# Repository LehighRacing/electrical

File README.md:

# hardware
Electronic Hardware Design

## Layout
- src
    - Individual hardware components
- lib
    - Library files common between components
- util
    - Utility tools

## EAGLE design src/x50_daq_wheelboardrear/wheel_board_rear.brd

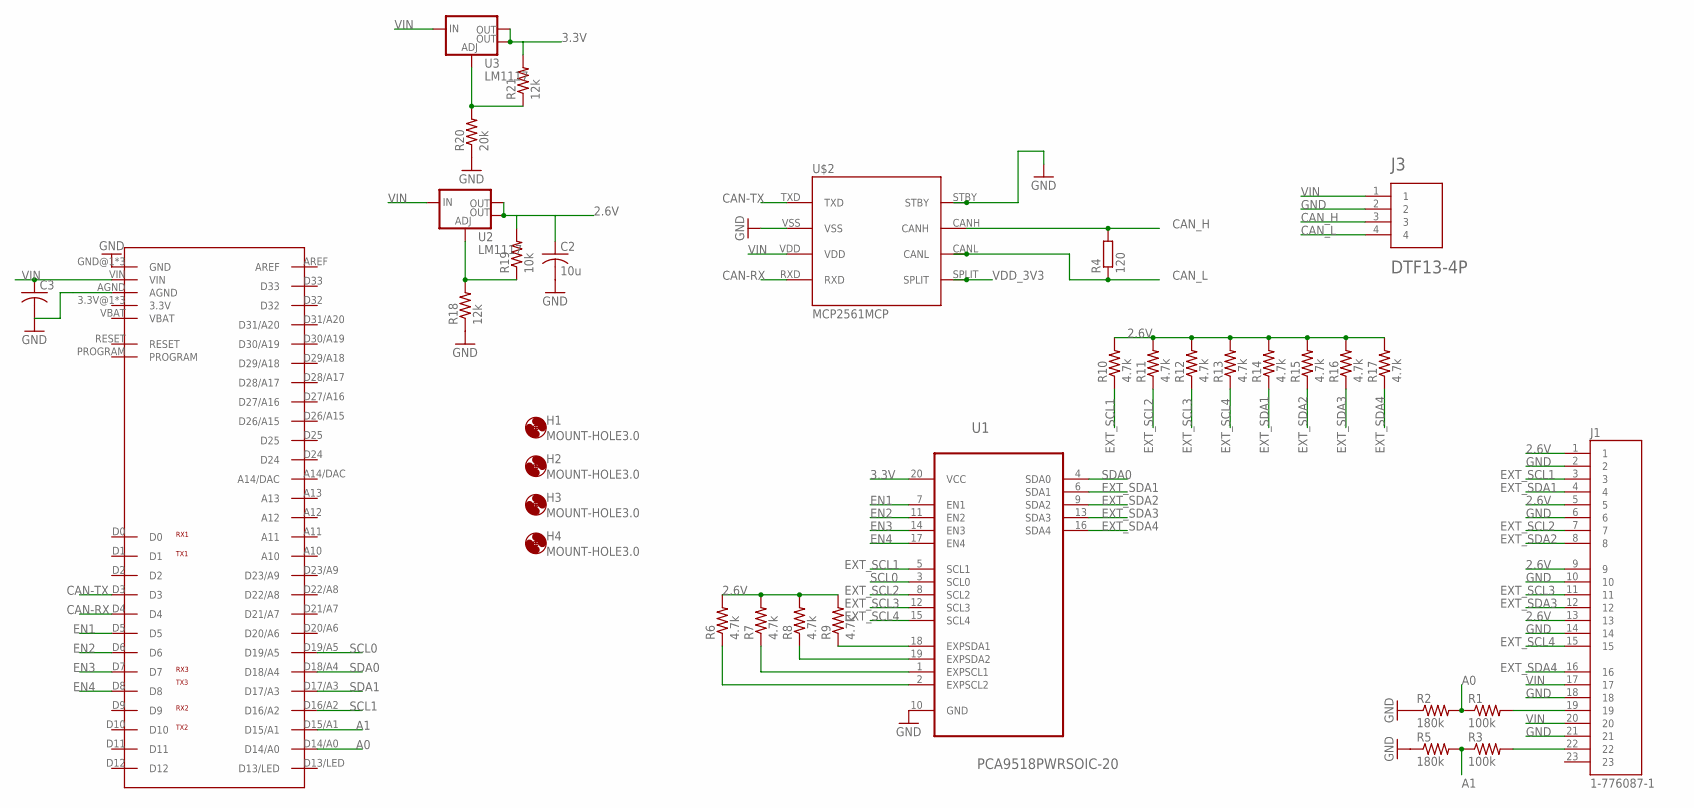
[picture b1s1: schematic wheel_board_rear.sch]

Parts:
C2: 10u; C050-024X044
C3: C-US050-024X044; C050-024X044
H1, H2, H3, H4: MOUNT-HOLE3.0; 3,0
J1: 1-776087-1; TE_1-776087-1
J3: DTF13-4P; TE_DTF13-4P
R1, R3: 100k; 0204/7
R2, R5: 180k; 0204/7
R4: 120; R0805
R6, R7, R8, R9, R10, R11, R12, R13, R14, R15, R16, R17: 4.7k; 0204/7
R18, R21: 12k; 0204/7
R19: 10k; 0204/7
R20: 20k; 0204/7
U1: PCA9518PWRSOIC-20; SOIC127P1032X265-20N
U2, U3: LM1117; SOT223
U$1: TEENSY3.1_ALL
U$2: MCP2561MCP; MCP2561_PDIP

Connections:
2.6V: C2.1, J1.1, J1.5, J1.9, J1.13, R6.2, R7.2, R8.2, R9.2, R10.2, R11.2, R12.2, R13.2, R14.2, R15.2, R16.2, R17.2, R19.2, U2.2 (OUT), U2.4 (OUT)
3.3V: R21.2, U1.20 (VCC), U3.2 (OUT), U3.4 (OUT)
A0: R1.1, R2.2, U$1.D14/A0
A1: R3.1, R5.2, U$1.D15/A1
CAN-RX: U$1.D4, U$2.RXD
CAN-TX: U$1.D3, U$2.TXD
CAN_H: J3.3, R4.2, U$2.CANH
CAN_L: J3.4, R4.1, U$2.CANL
EN1: U1.7 (EN1), U$1.D5
EN2: U1.11 (EN2), U$1.D6
EN3: U1.14 (EN3), U$1.D7
EN4: U1.17 (EN4), U$1.D8
EXT_SCL1: J1.3, R10.1, U1.5 (SCL1)
EXT_SCL2: J1.7, R11.1, U1.8 (SCL2)
EXT_SCL3: J1.11, R12.1, U1.12 (SCL3)
EXT_SCL4: J1.15, R13.1, U1.15 (SCL4)
EXT_SDA1: J1.4, R14.1, U1.6 (SDA1)
EXT_SDA2: J1.8, R15.1, U1.9 (SDA2)
EXT_SDA3: J1.12, R16.1, U1.13 (SDA3)
EXT_SDA4: J1.16, R17.1, U1.16 (SDA4)
GND: C2.2, C3.2, J1.2, J1.6, J1.10, J1.14, J1.18, J1.21, J3.2, R2.1, R5.1, R18.1, R20.1, U1.10 (GND), U$1.AGND, U$1.GND@1 (GND), U$1.GND@2 (GND), U$1.GND@3 (GND), U$2.STBY, U$2.VSS
unnamed: R9.1, U1.18 (EXPSDA1)
unnamed: R8.1, U1.19 (EXPSDA2)
unnamed: R7.1, U1.1 (EXPSCL1)
unnamed: R6.1, U1.2 (EXPSCL2)
unnamed: R20.2, R21.1, U3.1 (ADJ)
unnamed: J1.19, R1.2
unnamed: J1.22, R3.2
unnamed: R18.2, R19.1, U2.1 (ADJ)
SCL0: U1.3 (SCL0), U$1.D19/A5
SCL1: U$1.D16/A2
SDA0: U1.4 (SDA0), U$1.D18/A4
SDA1: U$1.D17/A3
VDD_3V3: U$2.SPLIT
VIN: C3.1, J1.17, J1.20, J3.1, U2.3 (IN), U3.3 (IN), U$1.VIN, U$2.VDD

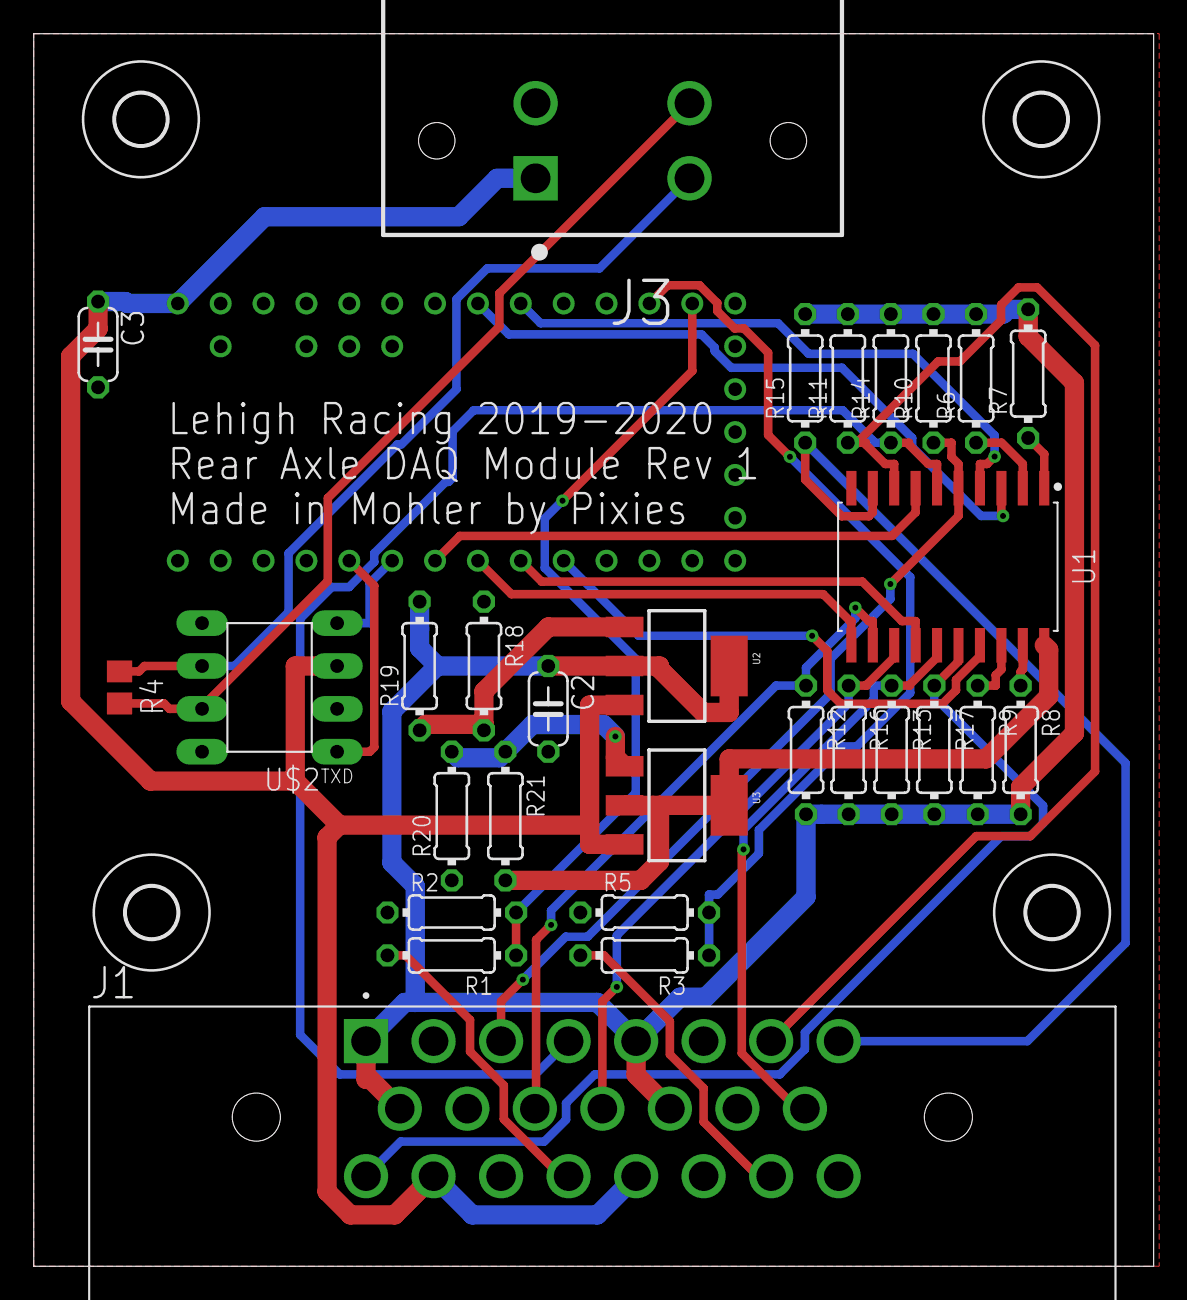
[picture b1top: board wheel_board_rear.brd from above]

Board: 2 copper layers, 66.3 x 73.0 mm, 34 parts (0 on the bottom side), 32 nets.

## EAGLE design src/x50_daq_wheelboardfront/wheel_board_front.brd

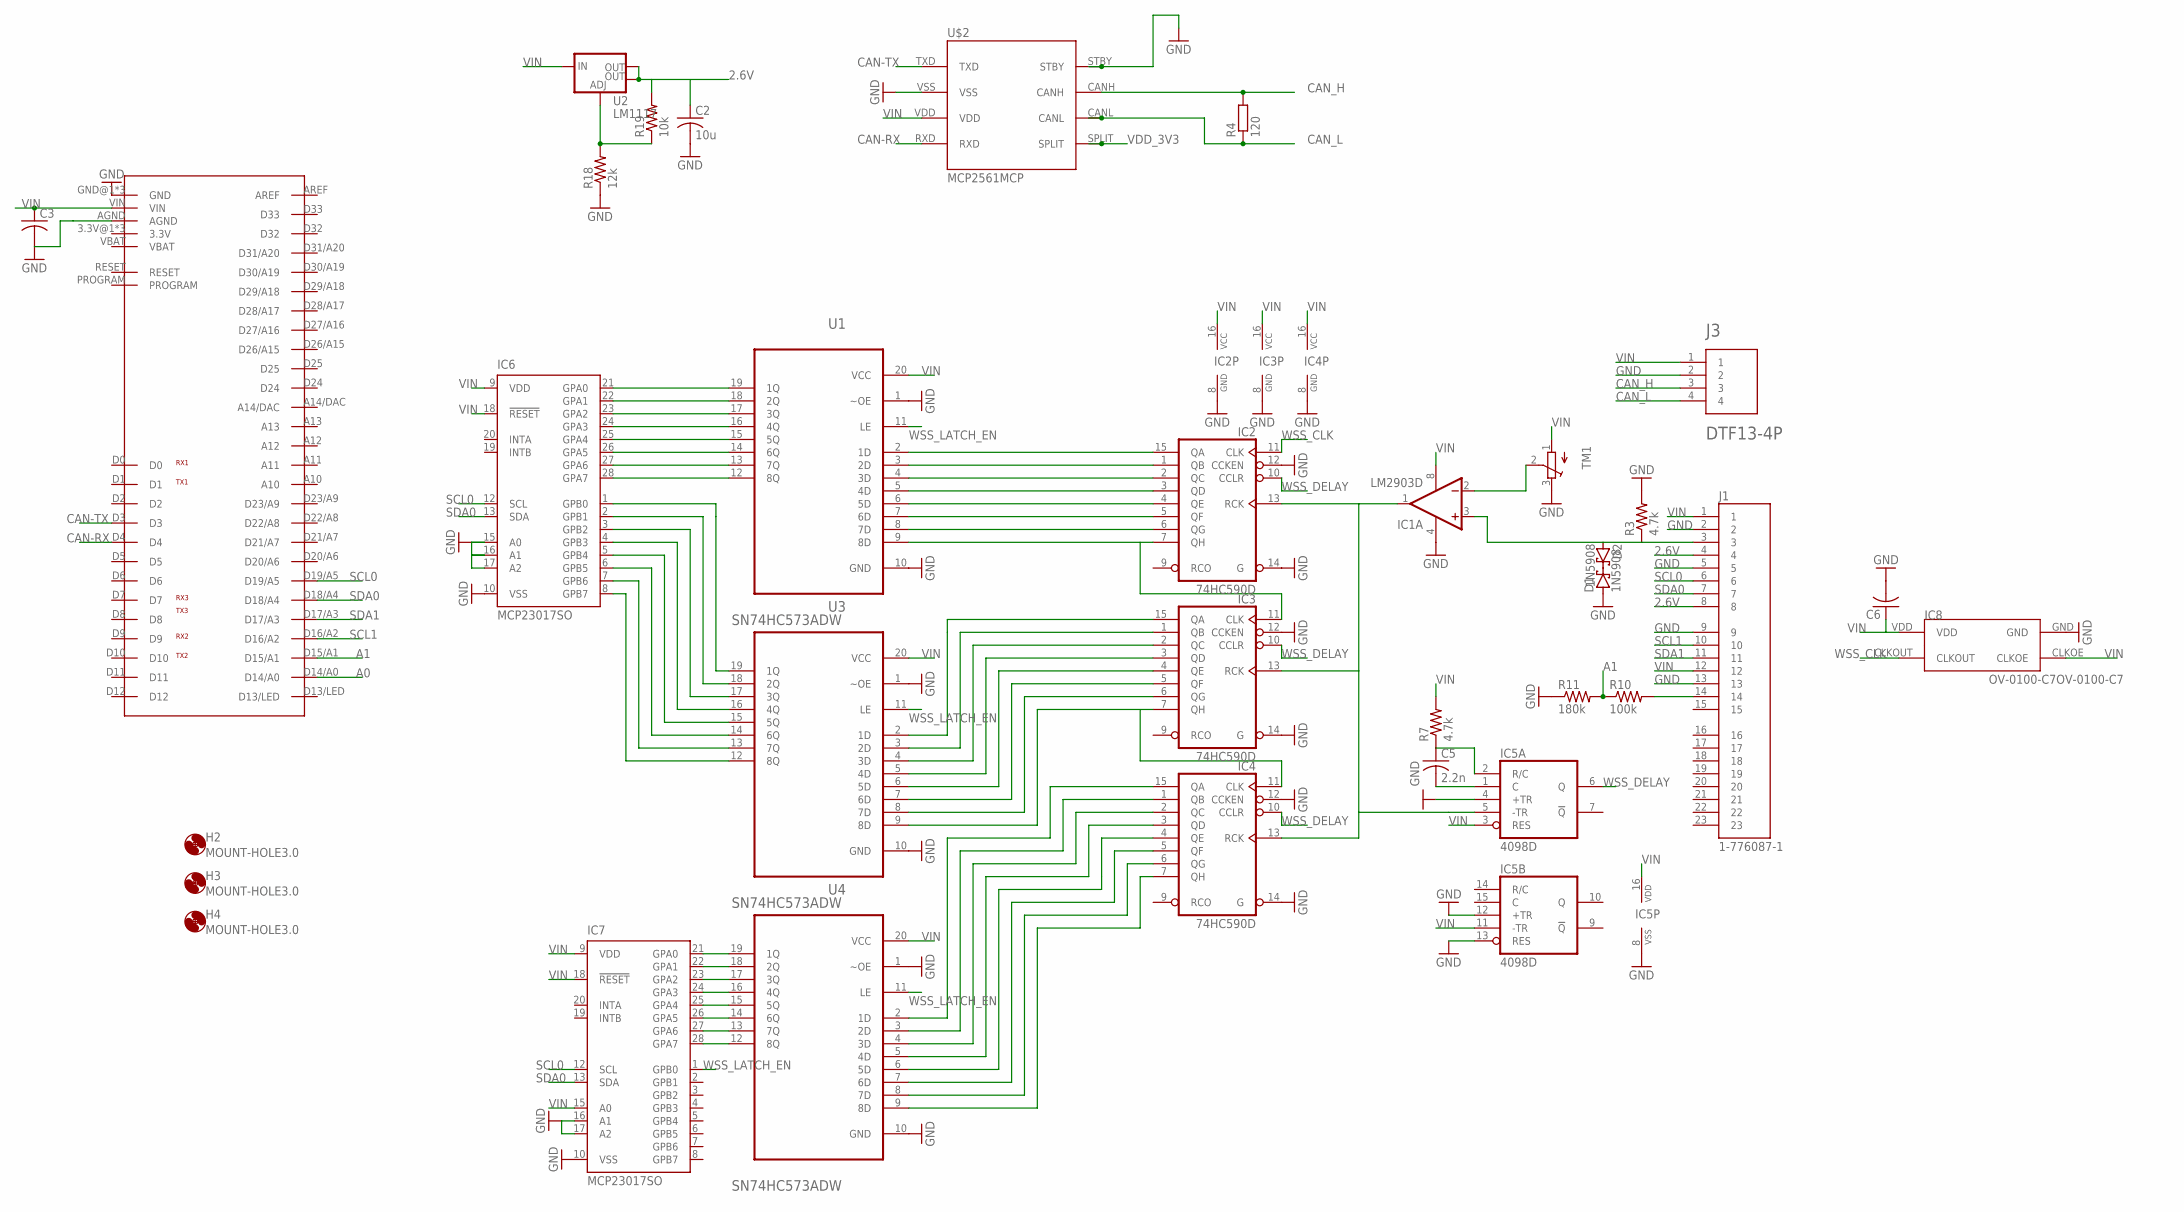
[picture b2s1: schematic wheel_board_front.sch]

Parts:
C2: 10u; C050-024X044
C3, C6: C-US050-024X044; C050-024X044
C5: 2.2n; C025-024X044
D1, D2: 1N5908; C4111-15
H2, H3, H4: MOUNT-HOLE3.0; 3,0
IC1: LM2903D; SO08
IC2, IC3, IC4: 74HC590D; SO16
IC5: 4098D; SO16
IC6, IC7: MCP23017SO; SO28W
IC8: OV-0100-C7OV-0100-C7; DFN320X150X100-4N
J1: 1-776087-1; TE_1-776087-1
J3: DTF13-4P; TE_DTF13-4P
R3, R7: 4.7k; 0204/7
R4: 120; R0805
R10: 100k; 0204/7
R11: 180k; 0204/7
R18: 12k; 0204/7
R19: 10k; 0204/7
TM1: TRIMPOTTC33X; TC33X
U1, U3, U4: SN74HC573ADW; SOIC127P1030X265-20N
U2: LM1117; SOT223
U$2: MCP2561MCP; MCP2561_PDIP
U$3: TEENSY3.1_ALL

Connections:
2.6V: C2.1, J1.4, J1.8, R19.2, U2.2 (OUT), U2.4 (OUT)
A0: U$3.D14/A0
A1: R10.1, R11.2, U$3.D15/A1
CAN-RX: U$2.RXD, U$3.D4
CAN-TX: U$2.TXD, U$3.D3
CAN_H: J3.3, R4.2, U$2.CANH
CAN_L: J3.4, R4.1, U$2.CANL
GND: C2.2, C3.2, C6.2, D1.A, IC1.4 (V-), IC2.8 (GND), IC2.12 (CCKEN), IC2.14 (G), IC3.8 (GND), IC3.12 (CCKEN), IC3.14 (G), IC4.8 (GND), IC4.12 (CCKEN), IC4.14 (G), IC5.4 (+TR), IC5.8 (VSS), IC5.12 (+TR), IC5.13 (RES), IC6.10 (VSS), IC6.15 (A0), IC6.16 (A1), IC6.17 (A2), IC7.10 (VSS), IC7.16 (A1), IC7.17 (A2), IC8.GND, J1.2, J1.5, J1.9, J1.13, J3.2, R3.2, R11.1, R18.1, TM1.3 (E), U1.1 (~OE), U1.10 (GND), U3.1 (~OE), U3.10 (GND), U4.1 (~OE), U4.10 (GND), U$2.STBY, U$2.VSS, U$3.AGND, U$3.GND@1 (GND), U$3.GND@2 (GND), U$3.GND@3 (GND)
unnamed: D2.A, IC1.3 (+IN), J1.3, R3.1
unnamed: J1.14, R10.2
unnamed: IC1.2 (-IN), TM1.2 (S)
unnamed: C5.1, IC5.2 (R/C), R7.1
unnamed: IC2.15 (QA), U1.2 (1D)
unnamed: C5.2, IC5.1 (C)
unnamed: IC1.1 (OUT), IC2.13 (RCK), IC3.13 (RCK), IC4.13 (RCK), IC5.5 (-TR)
unnamed: IC2.7 (QH), IC3.11 (CLK), U1.9 (8D)
unnamed: IC3.7 (QH), IC4.11 (CLK), U3.9 (8D)
unnamed: IC2.1 (QB), U1.3 (2D)
unnamed: D1.C, D2.C
unnamed: R18.2, R19.1, U2.1 (ADJ)
unnamed: IC2.2 (QC), U1.4 (3D)
unnamed: IC2.3 (QD), U1.5 (4D)
unnamed: IC2.4 (QE), U1.6 (5D)
unnamed: IC2.5 (QF), U1.7 (6D)
unnamed: IC2.6 (QG), U1.8 (7D)
unnamed: IC3.15 (QA), U3.2 (1D)
unnamed: IC3.1 (QB), U3.3 (2D)
unnamed: IC3.2 (QC), U3.4 (3D)
unnamed: IC3.3 (QD), U3.5 (4D)
unnamed: IC3.4 (QE), U3.6 (5D)
unnamed: IC3.5 (QF), U3.7 (6D)
unnamed: IC3.6 (QG), U3.8 (7D)
unnamed: IC4.15 (QA), U4.2 (1D)
unnamed: IC4.1 (QB), U4.3 (2D)
unnamed: IC4.2 (QC), U4.4 (3D)
unnamed: IC4.3 (QD), U4.5 (4D)
unnamed: IC4.4 (QE), U4.6 (5D)
unnamed: IC4.5 (QF), U4.7 (6D)
unnamed: IC4.6 (QG), U4.8 (7D)
unnamed: IC4.7 (QH), U4.9 (8D)
unnamed: IC6.21 (GPA0), U1.19 (1Q)
unnamed: IC6.22 (GPA1), U1.18 (2Q)
unnamed: IC6.23 (GPA2), U1.17 (3Q)
unnamed: IC6.24 (GPA3), U1.16 (4Q)
unnamed: IC6.25 (GPA4), U1.15 (5Q)
unnamed: IC6.26 (GPA5), U1.14 (6Q)
unnamed: IC6.27 (GPA6), U1.13 (7Q)
unnamed: IC6.28 (GPA7), U1.12 (8Q)
unnamed: IC6.1 (GPB0), U3.19 (1Q)
unnamed: IC6.2 (GPB1), U3.18 (2Q)
unnamed: IC6.3 (GPB2), U3.17 (3Q)
unnamed: IC6.4 (GPB3), U3.16 (4Q)
unnamed: IC6.5 (GPB4), U3.15 (5Q)
unnamed: IC6.6 (GPB5), U3.14 (6Q)
unnamed: IC6.7 (GPB6), U3.13 (7Q)
unnamed: IC6.8 (GPB7), U3.12 (8Q)
unnamed: IC7.21 (GPA0), U4.19 (1Q)
unnamed: IC7.22 (GPA1), U4.18 (2Q)
unnamed: IC7.23 (GPA2), U4.17 (3Q)
unnamed: IC7.24 (GPA3), U4.16 (4Q)
unnamed: IC7.25 (GPA4), U4.15 (5Q)
unnamed: IC7.26 (GPA5), U4.14 (6Q)
unnamed: IC7.27 (GPA6), U4.13 (7Q)
unnamed: IC7.28 (GPA7), U4.12 (8Q)
SCL0: IC6.12 (SCL), IC7.12 (SCL), J1.6, U$3.D19/A5
SCL1: J1.10, U$3.D16/A2
SDA0: IC6.13 (SDA), IC7.13 (SDA), J1.7, U$3.D18/A4
SDA1: J1.11, U$3.D17/A3
VDD_3V3: U$2.SPLIT
VIN: C3.1, C6.1, IC1.8 (V+), IC2.16 (VCC), IC3.16 (VCC), IC4.16 (VCC), IC5.3 (RES), IC5.11 (-TR), IC5.16 (VDD), IC6.9 (VDD), IC6.18 (!RESET), IC7.9 (VDD), IC7.15 (A0), IC7.18 (!RESET), IC8.CLKOE, IC8.VDD, J1.1, J1.12, J3.1, R7.2, TM1.1 (A), U1.20 (VCC), U2.3 (IN), U3.20 (VCC), U4.20 (VCC), U$2.VDD, U$3.VIN
WSS_CLK: IC2.11 (CLK), IC8.CLKOUT
WSS_DELAY: IC2.10 (CCLR), IC3.10 (CCLR), IC4.10 (CCLR), IC5.6 (Q)
WSS_LATCH_EN: IC7.1 (GPB0), U1.11 (LE), U3.11 (LE), U4.11 (LE)

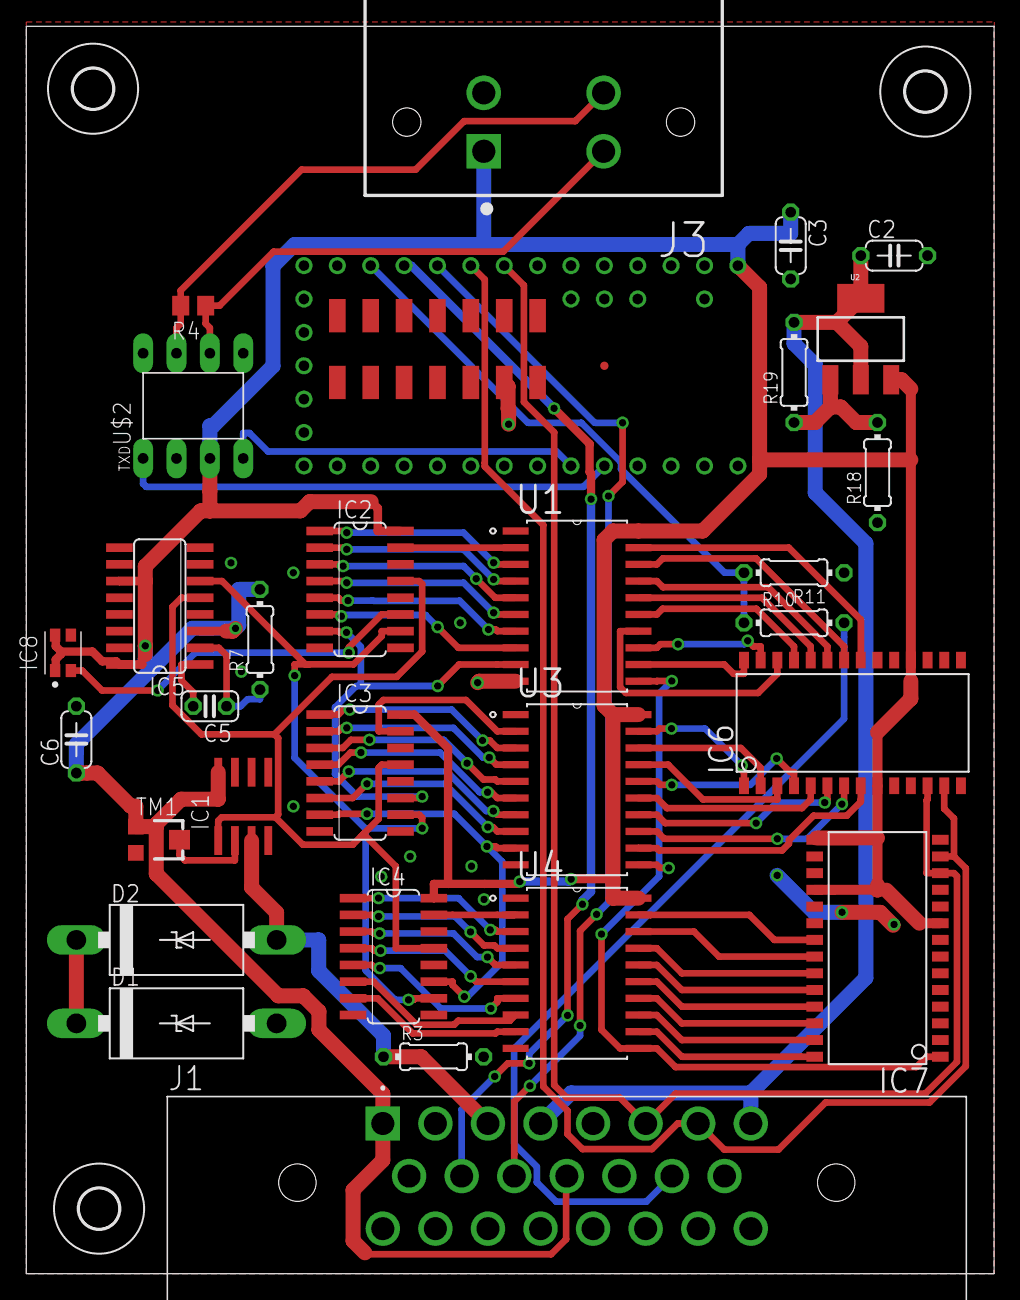
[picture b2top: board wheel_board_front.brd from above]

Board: 2 copper layers, 73.6 x 94.9 mm, 33 parts (1 on the bottom side), 71 nets.

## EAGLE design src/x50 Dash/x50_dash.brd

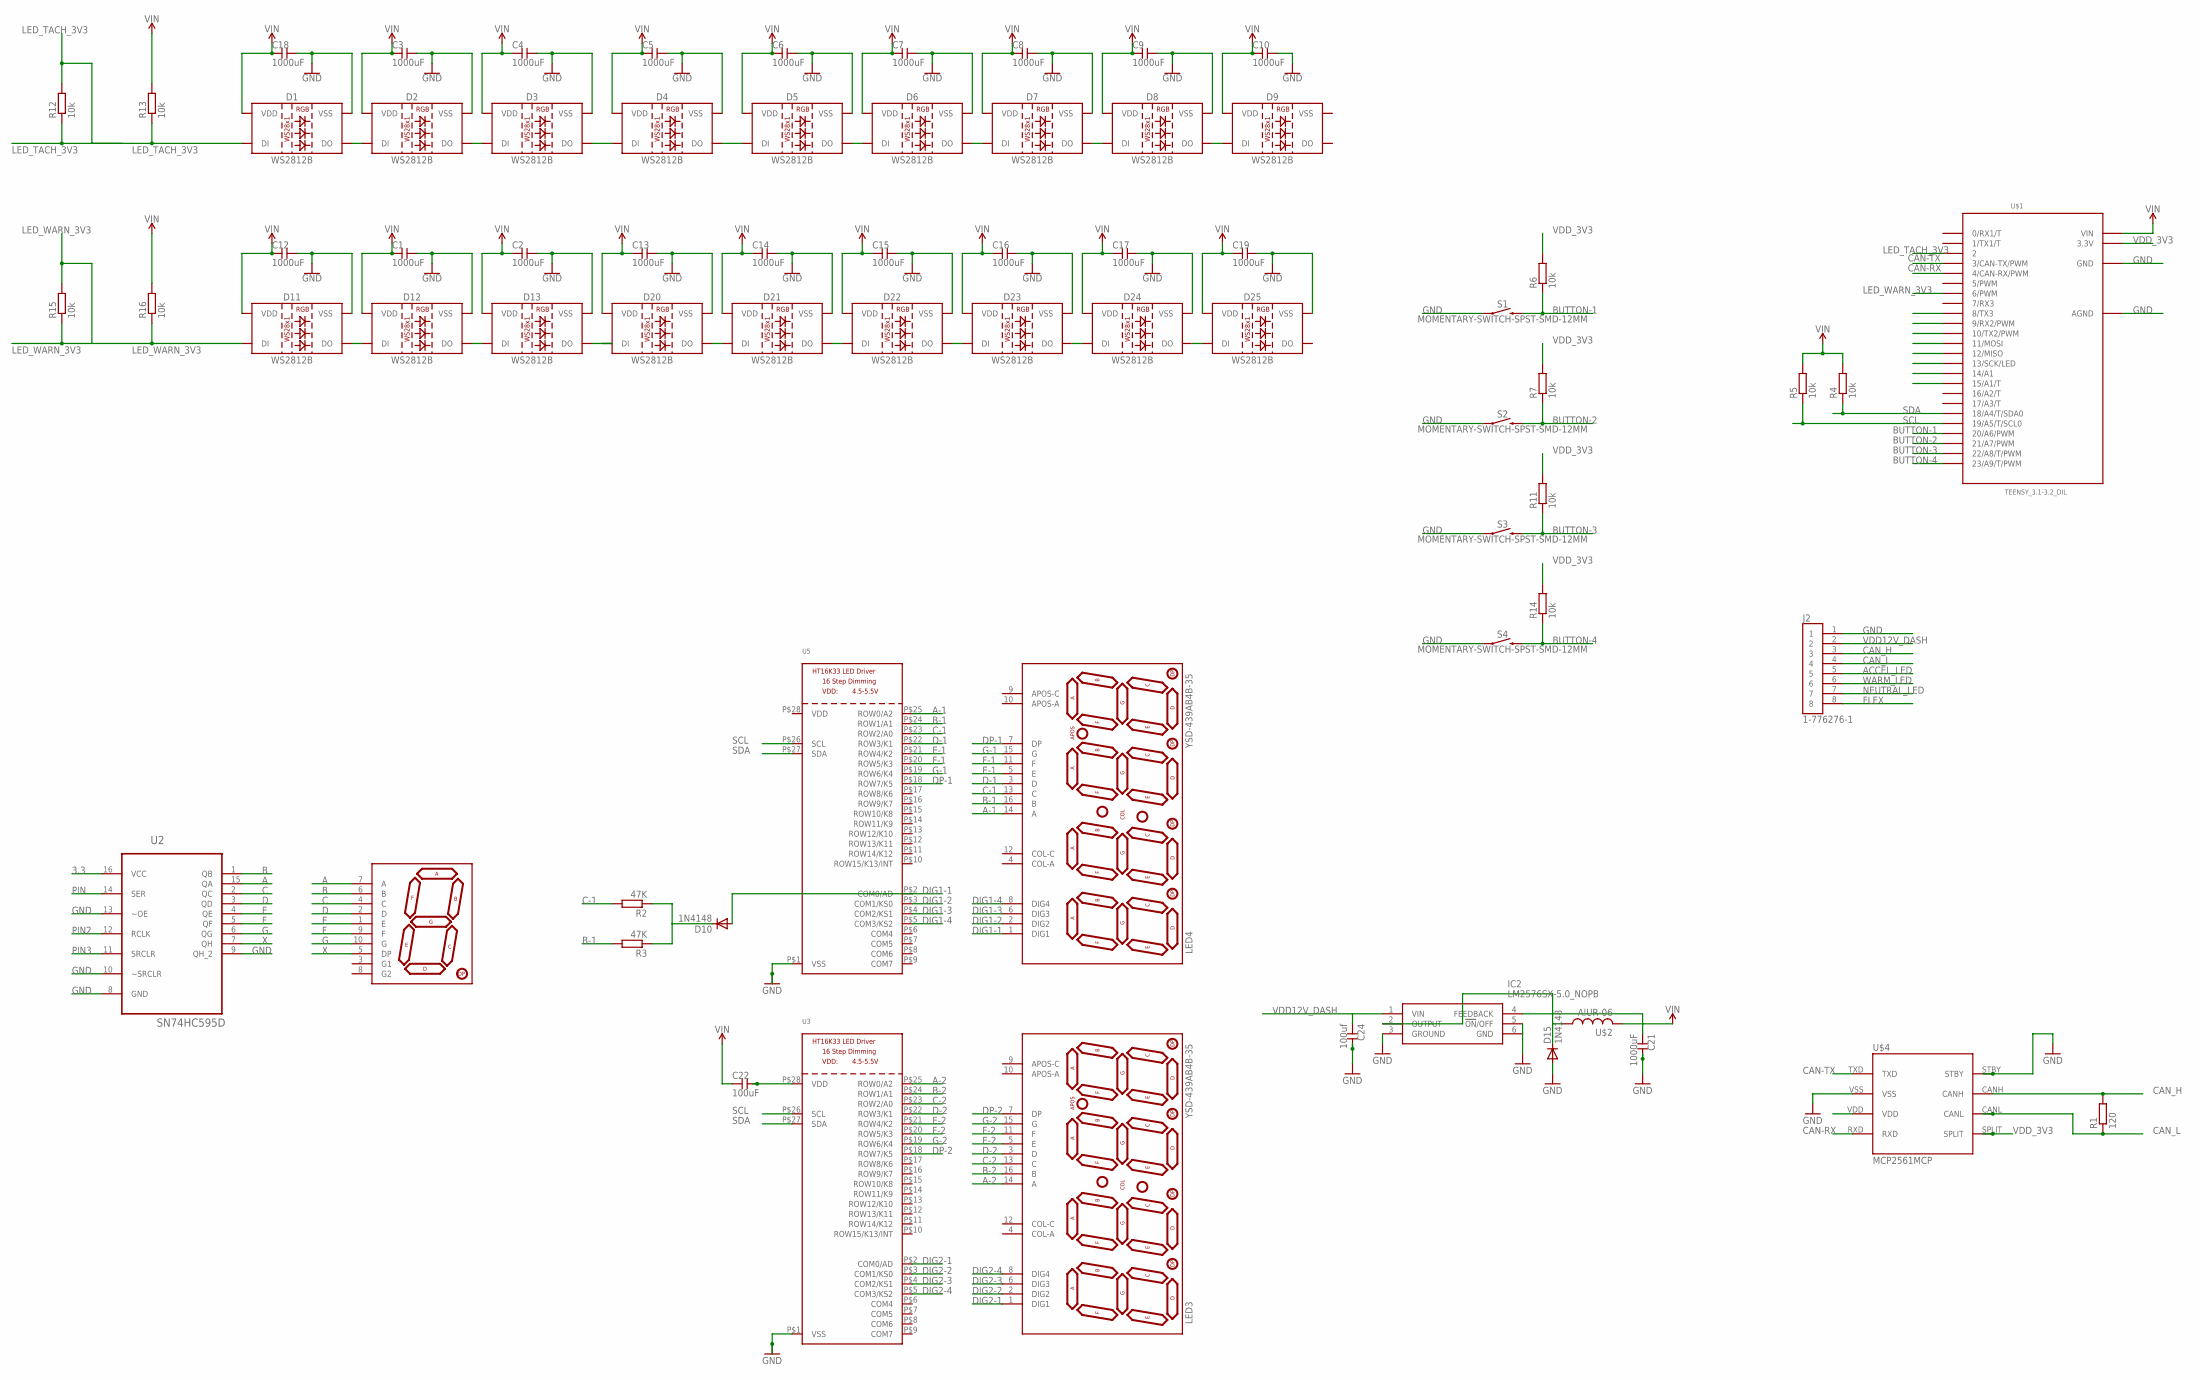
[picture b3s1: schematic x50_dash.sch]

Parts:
C1, C2, C3, C4, C5, C6, C7, C8, C9, C10, C12, C13, C14, C15, C16, C17, C18, C19, C21: 1000uF; 1005
C22: 100uF; 1005
C24: 100uf; 1005
D1, D2, D3, D4, D5, D6, D7, D8, D9, D11, D12, D13, D20, D21, D22, D23, D24, D25: WS2812B
D10, D15: 1N4148; DO35-10
IC2: LM2576SX-5.0_NOPB; KTT0005B
J2: 1-776276-1; TE_1-776276-1
LED3, LED4: YSD-439AB4B-35; 7-SEGMENT-4DIGIT-YOUNGSUN
R1: 120; R0805
R2, R3: 47K; R0805
R4, R5, R6, R7, R11, R12, R13, R14, R15, R16: 10k; R0805
S1, S2, S3, S4: MOMENTARY-SWITCH-SPST-SMD-12MM; TACTILE_SWITCH_SMD_12MM
U2: SN74HC595D; SOIC127P600X175-16N
U3, U5: HT16K33_SOP28; SOP28_300MIL
U$1: TEENSY_3.1-3.2_DIL; TEENSY_3.0-3.2&LC_DIL
U$2: AIUR-06
U$4: MCP2561MCP; MCP2561_PDIP
U$5: YSD-160AB3C-8; 7-SEGMENT-1"PTH

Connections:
3.3: U2.16 (VCC)
A: U2.15 (QA), U$5.7 (A)
A-1: LED4.14 (A), U5.P$25 (ROW0/A2)
A-2: LED3.14 (A), U3.P$25 (ROW0/A2)
ACCEL_LED: J2.5
B: U2.1 (QB), U$5.6 (B)
B-1: LED4.16 (B), R3.2, U5.P$24 (ROW1/A1)
B-2: LED3.16 (B), U3.P$24 (ROW1/A1)
BUTTON-1: R6.1, S1.3 (2), U$1.20/A6 (20/A6/PWM)
BUTTON-2: R7.1, S2.3 (2), U$1.21/A7 (21/A7/PWM)
BUTTON-3: R11.1, S3.3 (2), U$1.22/A8 (22/A8/T/PWM)
BUTTON-4: R14.1, S4.3 (2), U$1.23/A9 (23/A9/T/PWM)
C: U2.2 (QC), U$5.4 (C)
C-1: LED4.13 (C), R2.2, U5.P$23 (ROW2/A0)
C-2: LED3.13 (C), U3.P$23 (ROW2/A0)
CAN-RX: U$1.4 (4/CAN-RX/PWM), U$4.RXD, U$4.VDD
CAN-TX: U$1.3 (3/CAN-TX/PWM), U$4.TXD
CAN_H: J2.3, R1.2, U$4.CANH
CAN_L: J2.4, R1.1, U$4.CANL
D: U2.3 (QD), U$5.2 (D)
D-1: LED4.3 (D), U5.P$22 (ROW3/K1)
D-2: LED3.3 (D), U3.P$22 (ROW3/K1)
DIG1-1: D10.A, LED4.1 (DIG1), U5.P$2 (COM0/AD)
DIG1-2: LED4.2 (DIG2), U5.P$3 (COM1/KS0)
DIG1-3: LED4.6 (DIG3), U5.P$4 (COM2/KS1)
DIG1-4: LED4.8 (DIG4), U5.P$5 (COM3/KS2)
DIG2-1: LED3.1 (DIG1), U3.P$2 (COM0/AD)
DIG2-2: LED3.2 (DIG2), U3.P$3 (COM1/KS0)
DIG2-3: LED3.6 (DIG3), U3.P$4 (COM2/KS1)
DIG2-4: LED3.8 (DIG4), U3.P$5 (COM3/KS2)
DP-1: LED4.7 (DP), U5.P$18 (ROW7/K5)
DP-2: LED3.7 (DP), U3.P$18 (ROW7/K5)
E: U2.4 (QE), U$5.1 (E)
E-1: LED4.5 (E), U5.P$21 (ROW4/K2)
E-2: LED3.5 (E), U3.P$21 (ROW4/K2)
F: U2.5 (QF), U$5.9 (F)
F-1: LED4.11 (F), U5.P$20 (ROW5/K3)
F-2: LED3.11 (F), U3.P$20 (ROW5/K3)
FLEX: J2.8
G: U2.6 (QG), U$5.10 (G)
G-1: LED4.15 (G), U5.P$19 (ROW6/K4)
G-2: LED3.15 (G), U3.P$19 (ROW6/K4)
GND: C1.P$2 (2), C2.P$2 (2), C3.P$2 (2), C4.P$2 (2), C5.P$2 (2), C6.P$2 (2), C7.P$2 (2), C8.P$2 (2), C9.P$2 (2), C10.P$2 (2), C12.P$2 (2), C13.P$2 (2), C14.P$2 (2), C15.P$2 (2), C16.P$2 (2), C17.P$2 (2), C18.P$2 (2), C19.P$2 (2), C21.P$2 (2), C24.P$2 (2), D1.3 (VSS), D2.3 (VSS), D3.3 (VSS), D4.3 (VSS), D5.3 (VSS), D6.3 (VSS), D7.3 (VSS), D8.3 (VSS), D11.3 (VSS), D12.3 (VSS), D13.3 (VSS), D15.A, D20.3 (VSS), D21.3 (VSS), D22.3 (VSS), D23.3 (VSS), D24.3 (VSS), D25.3 (VSS), IC2.3 (GROUND), IC2.5 (!ON!/OFF), IC2.6 (GND), J2.1, S1.1, S2.1, S3.1, S4.1, U2.8 (GND), U2.9 (QH_2), U2.10 (~SRCLR), U2.13 (~OE), U3.P$1 (VSS), U5.P$1 (VSS), U$1.AGND, U$1.GND, U$4.STBY, U$4.VSS
LED_TACH_3V3: D1.4 (DI), R12.1, R12.2, R13.1, U$1.2
LED_WARN_3V3: D11.4 (DI), R15.1, R15.2, R16.1, U$1.6 (6/PWM)
MISO: U$1.12 (12/MISO)
MOSI: U$1.11 (11/MOSI)
unnamed: D10.C, R2.1, R3.1
unnamed: D1.2 (DO), D2.4 (DI)
unnamed: C22.P$2 (2), U3.P$28 (VDD)
unnamed: D12.2 (DO), D13.4 (DI)
unnamed: D7.2 (DO), D8.4 (DI)
unnamed: D8.2 (DO), D9.4 (DI)
unnamed: D11.2 (DO), D12.4 (DI)
unnamed: D15.C, IC2.2 (OUTPUT), U$2.P$1 (1)
unnamed: D2.2 (DO), D3.4 (DI)
unnamed: D3.2 (DO), D4.4 (DI)
unnamed: D4.2 (DO), D5.4 (DI)
unnamed: D5.2 (DO), D6.4 (DI)
unnamed: D6.2 (DO), D7.4 (DI)
unnamed: D20.2 (DO), D21.4 (DI)
unnamed: D21.2 (DO), D22.4 (DI)
unnamed: D22.2 (DO), D23.4 (DI)
unnamed: D23.2 (DO), D24.4 (DI)
unnamed: D24.2 (DO), D25.4 (DI)
NEUTRAL_LED: J2.7
OLED_CS: U$1.10 (10/TX2/PWM)
OLED_DC: U$1.15/A1 (15/A1/T)
OLED_RESET: U$1.14/A0 (14/A1)
PIN: U2.14 (SER)
PIN2: U2.12 (RCLK)
PIN3: U2.11 (SRCLR)
SCK: U$1.13 (13/SCK/LED)
SCL: R5.1, U3.P$26 (SCL), U5.P$26 (SCL), U$1.19/A5 (19/A5/T/SCL0)
SDA: R4.1, U3.P$27 (SDA), U5.P$27 (SDA), U$1.18/A4 (18/A4/T/SDA0)
SDCARD_CD: U$1.8 (8/TX3)
SDCARD_CS: U$1.9 (9/RX2/PWM)
VDD12V_DASH: C24.P$1 (1), IC2.1 (VIN), J2.2
VDD_3V3: R6.2, R7.2, R11.2, R14.2, U$1.3.3V, U$4.SPLIT
VIN: C1.P$1 (1), C2.P$1 (1), C3.P$1 (1), C4.P$1 (1), C5.P$1 (1), C6.P$1 (1), C7.P$1 (1), C8.P$1 (1), C9.P$1 (1), C10.P$1 (1), C12.P$1 (1), C13.P$1 (1), C14.P$1 (1), C15.P$1 (1), C16.P$1 (1), C17.P$1 (1), C18.P$1 (1), C19.P$1 (1), C21.P$1 (1), C22.P$1 (1), D1.1 (VDD), D2.1 (VDD), D3.1 (VDD), D4.1 (VDD), D5.1 (VDD), D6.1 (VDD), D7.1 (VDD), D8.1 (VDD), D9.1 (VDD), D11.1 (VDD), D12.1 (VDD), D13.1 (VDD), D20.1 (VDD), D21.1 (VDD), D22.1 (VDD), D23.1 (VDD), D24.1 (VDD), D25.1 (VDD), IC2.4 (FEEDBACK), R4.2, R5.2, R13.2, R16.2, U$1.VIN, U$2.P$2 (2)
WARM_LED: J2.6
X: U2.7 (QH), U$5.5 (DP)

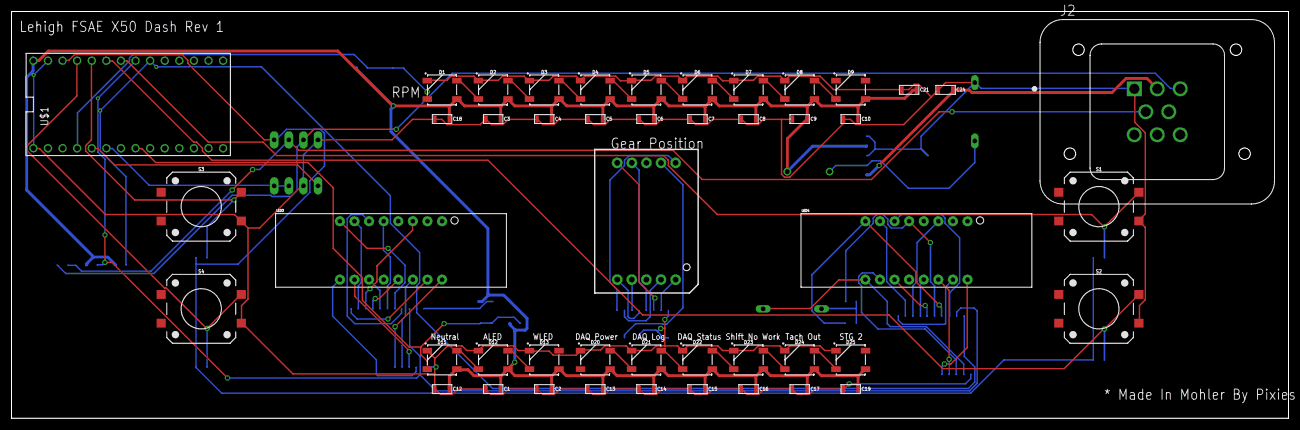
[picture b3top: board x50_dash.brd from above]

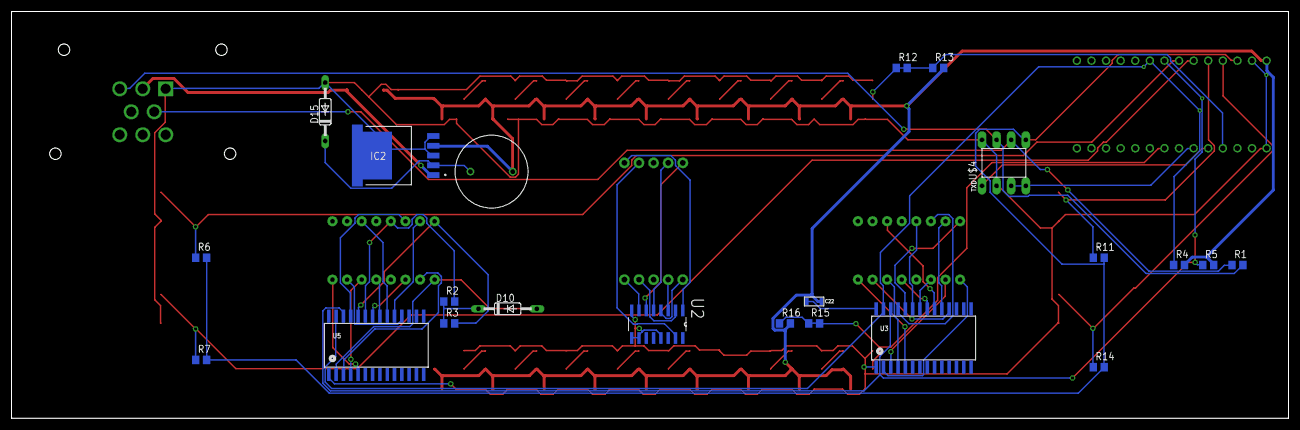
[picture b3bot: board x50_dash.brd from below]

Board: 2 copper layers, 222.2 x 70.8 mm, 69 parts (22 on the bottom side), 66 nets.

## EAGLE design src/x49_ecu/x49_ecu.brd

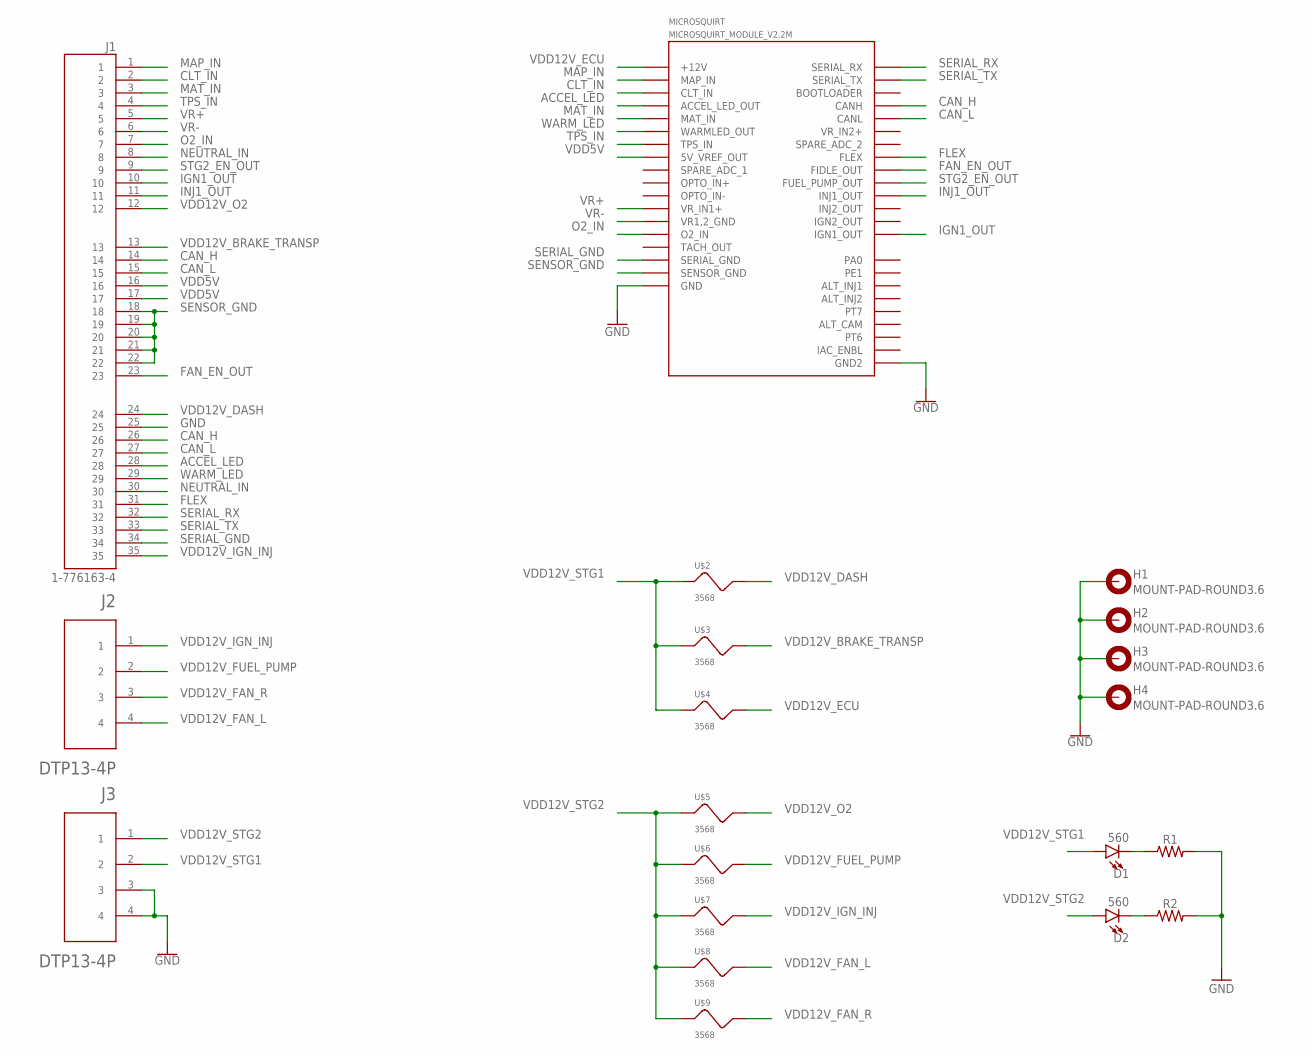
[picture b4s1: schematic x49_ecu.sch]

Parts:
D1, D2: 560; LED_5MM
H1, H2, H3, H4: MOUNT-PAD-ROUND3.6; 3,6-PAD
J1: 1-776163-4; TE_1-776163-4
J2, J3: DTP13-4P; TE_DTP13-4P
MICROSQUIRT: MICROSQUIRT_MODULE_V2.2M
R1, R2: AXIAL-0.3
U$2, U$3, U$4, U$5, U$6, U$7, U$8, U$9: 3568

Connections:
ACCEL_LED: J1.28, MICROSQUIRT.ACCEL_LED_OUT
CAN_H: J1.14, J1.26, MICROSQUIRT.CANH
CAN_L: J1.15, J1.27, MICROSQUIRT.CANL
CLT_IN: J1.2, MICROSQUIRT.CLT_IN
FAN_EN_OUT: J1.23, MICROSQUIRT.FIDLE_OUT
FLEX: J1.31, MICROSQUIRT.FLEX
GND: H1.B3,6, H2.B3,6, H3.B3,6, H4.B3,6, J1.25, J3.3, J3.4, MICROSQUIRT.GND1_1 (GND), MICROSQUIRT.GND1_2 (GND), MICROSQUIRT.GND1_3 (GND), MICROSQUIRT.GND1_4 (GND), MICROSQUIRT.GND1_5 (GND), MICROSQUIRT.GND1_6 (GND), MICROSQUIRT.GND1_7 (GND), MICROSQUIRT.GND1_8 (GND), MICROSQUIRT.GND2_1 (GND2), MICROSQUIRT.GND2_2 (GND2), R1.P$2 (2), R2.P$2 (2)
IGN1_OUT: J1.10, MICROSQUIRT.IGN1_OUT_1 (IGN1_OUT), MICROSQUIRT.IGN1_OUT_2 (IGN1_OUT)
INJ1_OUT: J1.11, MICROSQUIRT.INJ1_OUT_1 (INJ1_OUT), MICROSQUIRT.INJ1_OUT_2 (INJ1_OUT), MICROSQUIRT.INJ1_OUT_3 (INJ1_OUT), MICROSQUIRT.INJ1_OUT_4 (INJ1_OUT), MICROSQUIRT.INJ1_OUT_5 (INJ1_OUT)
MAP_IN: J1.1, MICROSQUIRT.MAP_IN
MAT_IN: J1.3, MICROSQUIRT.MAT_IN
unnamed: D1.K (C), R1.P$1 (1)
unnamed: D2.K (C), R2.P$1 (1)
NEUTRAL_IN: J1.8, J1.30
O2_IN: J1.7, MICROSQUIRT.O2_IN
SENSOR_GND: J1.18, J1.19, J1.20, J1.21, J1.22, MICROSQUIRT.SENSOR_GND
SERIAL_GND: J1.34, MICROSQUIRT.SERIAL_GND
SERIAL_RX: J1.32, MICROSQUIRT.SERIAL_RX
SERIAL_TX: J1.33, MICROSQUIRT.SERIAL_TX
STG2_EN_OUT: J1.9, MICROSQUIRT.FUEL_PUMP_OUT
TPS_IN: J1.4, MICROSQUIRT.TPS_IN
VDD5V: J1.16, J1.17, MICROSQUIRT.5V_VREF_OUT
VDD12V_BRAKE_TRANSP: J1.13, U$3.R_1 (2), U$3.R_2 (2)
VDD12V_DASH: J1.24, U$2.R_1 (2), U$2.R_2 (2)
VDD12V_ECU: MICROSQUIRT.+12V_1 (+12V), MICROSQUIRT.+12V_2 (+12V), U$4.R_1 (2), U$4.R_2 (2)
VDD12V_FAN_L: J2.4, U$8.R_1 (2), U$8.R_2 (2)
VDD12V_FAN_R: J2.3, U$9.R_1 (2), U$9.R_2 (2)
VDD12V_FUEL_PUMP: J2.2, U$6.R_1 (2), U$6.R_2 (2)
VDD12V_IGN_INJ: J1.35, J2.1, U$7.R_1 (2), U$7.R_2 (2)
VDD12V_O2: J1.12, U$5.R_1 (2), U$5.R_2 (2)
VDD12V_STG1: D1.A, J3.2, U$2.L_1 (1), U$2.L_2 (1), U$3.L_1 (1), U$3.L_2 (1), U$4.L_1 (1), U$4.L_2 (1)
VDD12V_STG2: D2.A, J3.1, U$5.L_1 (1), U$5.L_2 (1), U$6.L_1 (1), U$6.L_2 (1), U$7.L_1 (1), U$7.L_2 (1), U$8.L_1 (1), U$8.L_2 (1), U$9.L_1 (1), U$9.L_2 (1)
VR+: J1.5, MICROSQUIRT.VR_IN1+
VR-: J1.6, MICROSQUIRT.VR1,2_GND
WARM_LED: J1.29, MICROSQUIRT.WARMLED_OUT

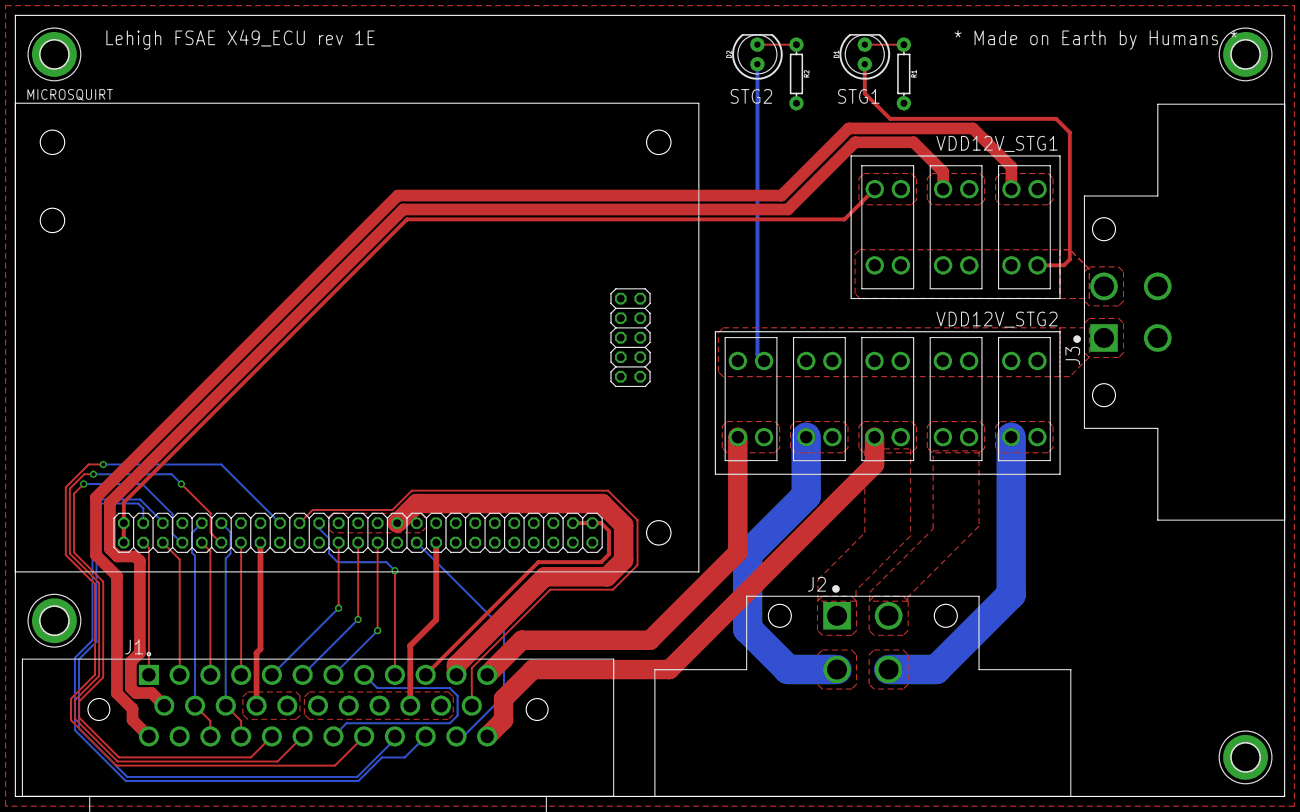
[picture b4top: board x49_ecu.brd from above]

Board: 2 copper layers, 165.1 x 101.6 mm, 20 parts (0 on the bottom side), 35 nets.

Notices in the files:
parts and their libraries:
SparkFun-IC-Power: Licensing: Creative Commons ShareAlike 4.0 International - https://creativecommons.org/licenses/by-sa/4.0
